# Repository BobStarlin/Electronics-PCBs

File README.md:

# Electronics-PCBs
4Digit 7 segment display, driven by the MAX7219CNG

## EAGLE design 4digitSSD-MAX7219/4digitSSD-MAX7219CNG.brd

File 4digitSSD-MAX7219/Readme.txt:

This is an eagle cadsoft (Free version) of a 4 digit 7 segment display breakout board. 
The driver IC is the Maxim MAX7219CNG. This uses the through hole version because that 
is what I had on hand.

The ISET pot could be swapped out with a SMD resistor of about 9k ohms, using these parts.

This is a 2 layer board, again, because I had two layer copper boards, and it made routing
easy and fast. A single layer board could be done, with time and patience. I may get to that
or maybe not. This is a busy work project while it is raining outside.

See datasheet for calculations, never assume this will work with your components without verifying.

Use at your own risk.
No warranty expressed or implied.

I hope you like it, and I am sorry if it isnt as professional as some of you could make it.
Bob

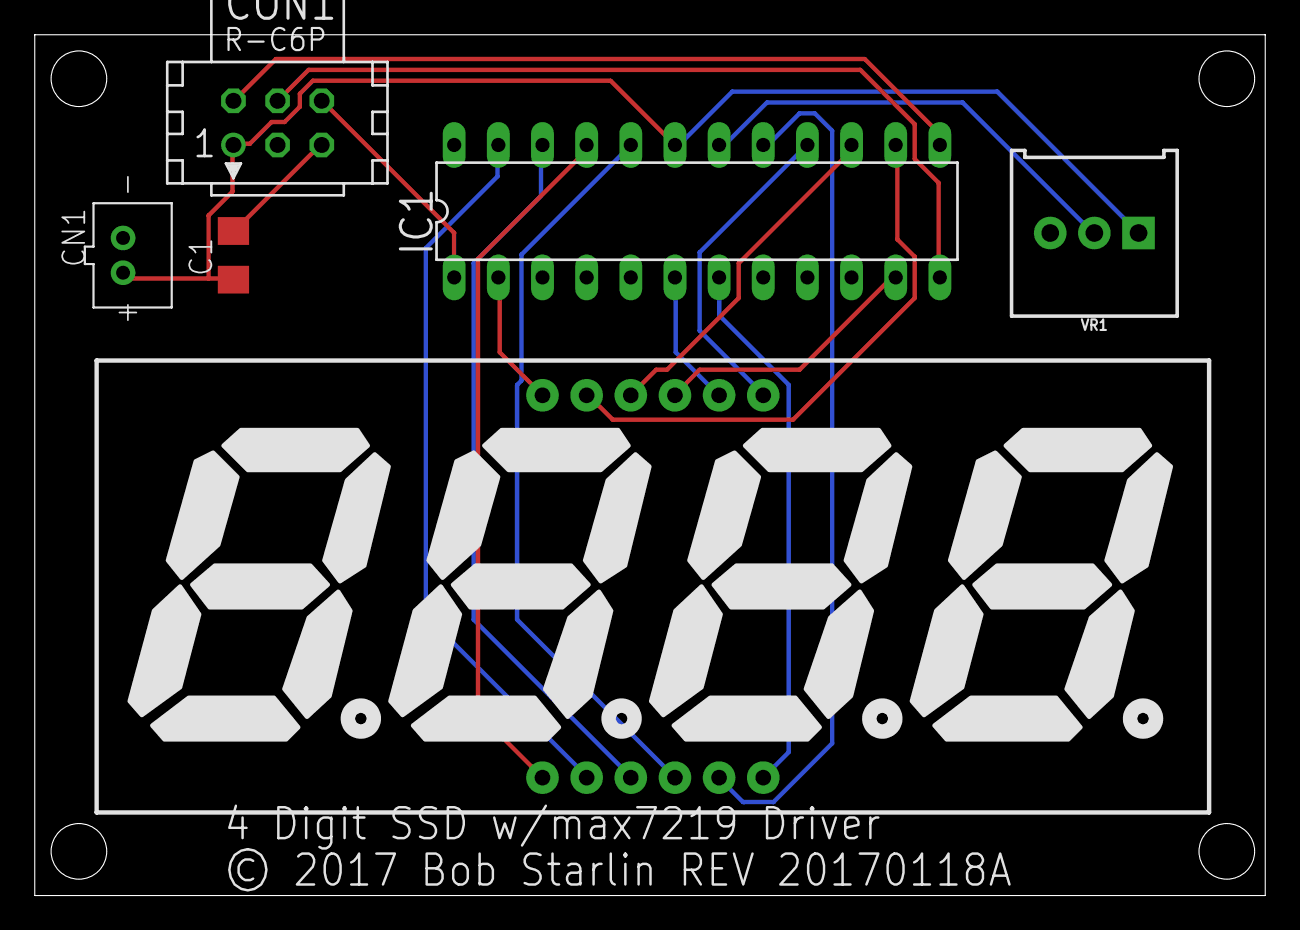
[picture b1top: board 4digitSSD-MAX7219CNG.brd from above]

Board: 2 copper layers, 70.8 x 49.5 mm, 6 parts (0 on the bottom side), 18 nets.

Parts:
C1: .1uF; C1206
CN1: Aux PWR; JST-PH-2-THM
CON1: uC CONN; CON06
IC1: MAX7219CNG; DIL24-3
U$1: 7-SEGMENT-4DIGIT-COUNTERPTH; 7-SEGMENT-4DIGIT-COUNTER
VR1: 10k; TRIMPOT-PTH-3386U

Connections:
A: IC1.14, U$1.11
B: IC1.16, U$1.7
C: IC1.20, U$1.4
CLK: CON1.2, IC1.13
D: IC1.23, U$1.2
D1: IC1.2, U$1.12
D2: IC1.11, U$1.9
D3: IC1.6, U$1.8
D4: IC1.7, U$1.6
DIN: CON1.6, IC1.1
DP: IC1.22, U$1.3
E: IC1.21, U$1.1
F: IC1.15, U$1.10
G: IC1.17, U$1.5
GND: C1.2, CN1.2, CON1.5, IC1.4, IC1.9, VR1.3
LOAD: CON1.4, IC1.12
unnamed: IC1.18, VR1.2
VCC: C1.1, CN1.1, CON1.1, IC1.19, VR1.1

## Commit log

2017-01-18 :boom::camel: Added .gitattributes & .gitignore files
2017-01-18 4 digit seven segment display, driven by the MAX7219CNG
    Breakout board for a 4 digit common cathode 7 segment display, driven by
    the Maxim MAX7219CNG Driver. It includes an optional JST power
    connection, and a potentiometer for ISET on the MAX7219 chip. See data
    sheet for details on segment current calculation. This chip only uses
    one 4 digit SSD, while the MAX7219 can drive more.
2017-01-18 ReadMe
    Comments regarding this design.
2017-01-18 Create README.md
    Some of my electronics projects, Not guaranteed to be done, tested or even viable.
    Use at your own risk.
    No warranty expressed or implied.
2017-01-18 Set theme jekyll-theme-slate
2017-01-19 Add files via upload
    Minor routing updates. Added filter capacitor across supply.
    Revision 20170118A
    No warranty expressed or implied in any form. Use at your own risk.
    © 2017 Bob Starlin
2017-01-19 REV 20170118A
    slight routing changes. Added power supply filter capacitor.

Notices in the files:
4digitSSD-MAX7219/4digitSSD-MAX7219CNG.brd:
© 2017 Bob Starlin REV 20170118A
parts and their libraries:
SparkFun-Displays: Licensing: CC v3.0 Share-Alike You are welcome to use this library for commercial purposes.
SparkFun-Resistors: Licensing: Creative Commons ShareAlike 4.0 International - https://creativecommons.org/licenses/by-sa/4.0
